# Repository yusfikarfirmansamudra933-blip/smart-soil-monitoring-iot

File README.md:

# Smart Soil Monitoring IoT

Aplikasi web profesional bergaya **Industrial IoT** untuk memantau kondisi tanah, energi tenaga surya, dan status pulsa modem secara *real-time* maupun historis menggunakan **ESP32-S3 N16R8**, **2× Sensor Arus & Tegangan DC INA226**, **Solar Charge Controller MPPT CN3791**, **Active Buzzer (Alarm Sisa Pulsa Modem 4G)**, **DS18B20 Waterproof**, **Capacitive Soil Moisture Sensor**, **Sensor pH Tanah Output Analog ADC + DMS**, dan **Modem 4G LTE**.

- **Production Web App**: https://smart-soil-monitoring-iot.vercel.app
- **Default Device ID**: `SOIL-001`
- **Database**: Supabase PostgreSQL

---

## Fitur Utama
- **Responsif & PWA**: Mendukung Android, tablet, dan desktop dengan App Manifest (`/manifest.json`), Service Worker (`/sw.js`), Splash Screen, dan deteksi Offline State.
- **Monitoring Tanah Real-Time**:
  1. **Soil pH (Analog ADC + DMS)**: Nilai pH terkini, grafik perubahan, status Asam/Netral/Basa, riwayat pengukuran, dan status koneksi sensor.
  2. **Soil Moisture (Capacitive Soil Moisture + DMS)**: Pembacaan kelembapan terkalibrasi (`%`) & nilai mentah (`Raw Value`), status Kering/Normal/Basah, riwayat, dan status koneksi.
  3. **Soil Temperature (DS18B20 Waterproof)**: Suhu tanah dalam °C, grafik perubahan, status suhu, riwayat, dan status sensor.
- **Dual-Channel Energy Monitoring (2× INA226 + CN3791 MPPT)**:
  - **INA226 #1 (`0x40`)**: Memantau **Tegangan (V), Arus (A), dan Daya (W) Panel Surya** secara real-time.
  - **INA226 #2 (`0x41`)**: Memantau **Tegangan (V), Arus (A), dan Daya (W) Baterai** secara real-time.
  - Tidak membuat data energi palsu (menampilkan `Not Available` jika INA226 belum terdeteksi).
- **Fitur Peringatan Pulsa Modem 4G + Active Buzzer**:
  - Memantau sisa pulsa Modem 4G (`modem_credit_rp`) dan otomatis membunyikan **Active Buzzer (`GPIO 21`)** serta memicu alarm kritis di dashboard saat pulsa turun di bawah ambang batas (default `< Rp 10.000`).
- **Grafik & Riwayat Interaktif**: Filter rentang waktu (`1 jam`, `6 jam`, `24 jam`, `7 hari`, `30 hari`), filter tanggal, tabel riwayat, **Export CSV**, dan **Export PDF**.
- **Sistem Alarm Otomatis (10 Parameter)**: Evaluasi otomatis pH, kelembapan, suhu, tegangan baterai, status ESP32-S3, koneksi sensor, modem 4G, dan **sisa pulsa modem (Active Buzzer)**.
- **Demo Mode vs Live Hardware Mode**: Semua data simulasi berlabel `DEMO` (`is_demo: true`) dan dipisahkan dari data perangkat nyata (`is_demo: false`) di PostgreSQL.

---

## Komponen Utama Perangkat Keras
1. **ESP32-S3 N16R8** — Otak utama (Dual-core, 16MB Flash, 8MB OPI PSRAM, I2C, ADC1, UART).
2. **2× Sensor Arus & Tegangan DC INA226** — 16-bit I2C bidirectional monitor (`0x40` untuk **Panel Surya**, `0x41` untuk **Baterai**).
3. **CN3791** — MPPT Solar Charge Controller untuk pengisian baterai efisien dari panel surya.
4. **Active Buzzer** — Alarm suara lokal ketika sisa pulsa Modem 4G menipis.
5. **DS18B20 Waterproof** — Sensor suhu tanah digital tahan air (1-Wire).
6. **Capacitive Soil Moisture Sensor** — Sensor kelembapan tanah kapasitif anti-korosi.
7. **Sensor pH Tanah Output Analog ADC + DMS** — Arsitektur *Driver Sensor Modular*.
8. **Modem 4G LTE (MiFi Bolt ZTE MF90 Unlock All Operator)** — Koneksi internet lapangan & pembacaan SMS kuota/pulsa operator.
9. **Panel Surya & Baterai** — Sumber daya mandiri 24 jam.
10. **DC-DC Converter 5V, Sekering (Fuse), & Distribusi Daya**.

---

## Diagram Blok Wiring Keseluruhan

```text
                SISTEM TENAGA SURYA, CN3791 MPPT & 2× INA226
  ┌─────────────────┐     ┌──────────────────────┐     ┌───────────────────────┐
  │   Panel Surya   │────▶│  INA226 #1 (0x40)    │────▶│  CN3791 MPPT Charger  │
  │    (PV+ / PV-)  │     │  (Ukur V, A, W PV)   │     │  [IN+ / IN-]          │
  └─────────────────┘     └──────────┬───────────┘     │  [BAT+ / BAT-]        │
                                     │ I2C (SDA/SCL)   └───────────┬───────────┘
                                     │                             ▼
                                     │                 ┌───────────────────────┐
                                     │                 │  INA226 #2 (0x41)     │
                                     │                 │  (Ukur V, A, W Batt)  │
                                     │                 └─────┬───────────┬─────┘
                                     │ I2C (GPIO 8/9)        │ I2C       │ Fuse
                                     └───────────────────────┘           ▼
                                                               ┌───────────────────┐
                                                               │ Baterai + DC-DC   │
                                                               │ Regulasi 5V Stabil│
                                                               └────┬─────────┬────┘
                                                            5V/GND  │         │ 5V/GND
                                                     ┌──────────────┘         └──────────────┐
                                                     ▼                                       ▼
                                           ┌──────────────────┐                    ┌─────────────────────────────┐
                                           │    Modem 4G      │◀─ WiFi / UART2 ───▶│       ESP32-S3 N16R8        │
                                           │  (Cek Pulsa+Net) │  (GPIO 17 / 18)    │  5V | 3.3V | GND | I2C 8/9  │
                                           └──────────────────┘                    └─┬──────┬──────┬──────┬──────┘
                                                                                     │      │      │      │
                ┌────────────────────────────────────────────────────────────────────┘      │      │      └──────────────────┐
                ▼                                 ▼                                         ▼                                ▼
    ┌───────────────────────┐         ┌────────────────────────┐               ┌──────────────────────────┐      ┌──────────────────────┐
    │   DS18B20 Waterproof  │         │ Capacitive Soil Moist. │               │  pH Analog ADC + DMS     │      │    Active Buzzer     │
    │  DATA ──▶ GPIO 4      │         │   AOUT ──▶ GPIO 5      │               │ pH ──▶ GPIO 6 (ADC1)     │      │  SIG ──▶ GPIO 21     │
    │  + Pull-up 4.7kΩ 3.3V │         │   VCC ──▶ 3.3V         │               │ DMS ──▶ GPIO 7 (ADC1)    │      │ (Alarm Pulsa Menipis)│
    └───────────────────────┘         └────────────────────────┘               └──────────────────────────┘      └──────────────────────┘
```

---

## 1. Wiring Tenaga Surya, CN3791 MPPT & 2× INA226

### A. Jalur Daya Utama (High-Side Current Sensing)
| Dari Komponen | Ke Komponen | Keterangan |
|---|---|---|
| Panel Surya (`PV+`) | **INA226 #1 (`0x40`)** `VIN+` | Jalur positif panel masuk ke shunt INA226 #1 |
| **INA226 #1 (`0x40`)** `VIN-` | **CN3791** Terminal `IN+` (`PV+`) | Arus panel terukur sebelum masuk ke CN3791 |
| Panel Surya (`PV-`) | **CN3791** `IN-` (`GND`) | Satukan ke Common Ground (`GND`) |
| **CN3791** Terminal `BAT+` | **INA226 #2 (`0x41`)** `VIN+` | Jalur pengisian/pemakaian baterai masuk ke shunt INA226 #2 |
| **INA226 #2 (`0x41`)** `VIN-` | **Sekering (Fuse)** → Baterai (`+`) & Input DC-DC 5V | Mengukur tegangan, arus charge (+), dan arus discharge (-) baterai |
| Baterai (`-`) | **CN3791** `BAT-` (`GND`) & Common Ground | Semua `GND` (CN3791, 2× INA226, ESP32-S3, Modem 4G) wajib tersambung |
| Output DC-DC 5V (`5V` / `GND`) | Pin `5V` ESP32-S3 N16R8 & Daya `5V` Modem 4G | Pastikan output stabil **5.0V (≥ 2A)** sebelum disambung |

### B. Wiring Dual Bus I2C 2× INA226 ke ESP32-S3 N16R8 (Tanpa Jumper `A0`)
Kedua modul INA226 tetap memakai alamat standar `0x40` dengan memanfaatkan 2 jalur Hardware I2C terpisah pada ESP32-S3 (`Wire` & `Wire1`):

| Pin INA226 | INA226 #1 — Panel Surya (`Wire` / `0x40`) | INA226 #2 — Baterai 3S (`Wire1` / `0x40`) |
|---|---|---|
| `VCC` | `3.3V` ESP32-S3 | `3.3V` ESP32-S3 |
| `GND` | `GND` ESP32-S3 | `GND` ESP32-S3 |
| `SDA` | **`GPIO 8`** ESP32-S3 | **`GPIO 10`** ESP32-S3 |
| `SCL` | **`GPIO 9`** ESP32-S3 | **`GPIO 11`** ESP32-S3 |
| `VBS` (`VBUS`) | Sambung ke `IN-` / `IN+` (PV+) | Sambung ke `IN-` / `IN+` (BAT+) |

---

## 2. Wiring Sensor Tanah, Active Buzzer & Modem 4G ke ESP32-S3 N16R8

> **PERINGATAN PIN ESP32-S3 N16R8:**
> Pada varian **N16R8 (Octal OPI PSRAM)**, **`GPIO 35`, `GPIO 36`, dan `GPIO 37` digunakan internal oleh PSRAM** dan **TIDAK BOLEH** dipakai untuk sensor. Semua pin di bawah ini 100% aman dan berada di `ADC1` (tidak bentrok dengan WiFi).

| Komponen | Pin Modul | Pin ESP32-S3 N16R8 | Keterangan |
|---|---|---|---|
| **DS18B20 Waterproof** | `VCC` (Merah) / `GND` (Hitam) / `DATA` (Kuning) | `3.3V` / `GND` / **`GPIO 4`** | Wajib pasang resistor **pull-up 4.7 kΩ** antara `GPIO 4` dan `3.3V` |
| **Capacitive Soil Moisture** | `VCC` / `GND` / `AOUT` | `3.3V` / `GND` / **`GPIO 5`** | `ADC1_CH4` — gunakan suplai 3.3V agar output ≤3.3V |
| **Modul DMS (Depoinovasi)** | Kabel 1: `Hitam / Coklat` | **`GND`** | Ground Modul DMS |
| **Modul DMS (Depoinovasi)** | Kabel 2: `Putih / Merah` | **`3.3V`** | Tegangan suplai `Vin / 3V3` Modul DMS |
| **Modul DMS + Probe pH** | Kabel 3: `Abu-abu / Oren` | **Kabel `Hitam` Probe pH** | Kabel `Putih` Probe pH disambung langsung ke **`GND` ESP32-S3** |
| **Modul DMS (ADC pH)** | Kabel 4: `Ungu / Kuning` | **`GPIO 6`** (`ADC1_CH5`) | Pengganti `D34` pada ESP32 biasa (aman dari PSRAM ESP32-S3) |
| **Modul DMS (Digital/D13)** | Kabel 5: `Biru / Hijau` | **`GPIO 7`** | Pengganti `D13` pada ESP32 biasa |
| **Active Buzzer (Alarm Pulsa)** | `VCC / (+)` / `GND / (-)` | **`GPIO 21`** / `GND` | Gunakan transistor NPN `S8050` + resistor `1 kΩ` untuk buzzer 5V 2-pin |
| **Modem 4G (MiFi Bolt ZTE MF90)** | Port Micro-USB `5V` / WiFi AP | `5V DC-DC` / WiFi | Suplai `5V` stabil dari DC-DC Buck Converter; ESP32-S3 konek ke WiFi MiFi ZTE MF90 & baca SMS operator via `192.168.1.1` / `192.168.0.1` |

---

## 3. Cara Upload Firmware ke ESP32-S3 N16R8

File firmware berada di folder `firmware/esp32_smart_soil/`:
- [esp32_smart_soil.ino](firmware/esp32_smart_soil/esp32_smart_soil.ino)
- [sensor_drivers.h](firmware/esp32_smart_soil/sensor_drivers.h)
- [modem_quota_reader.h](firmware/esp32_smart_soil/modem_quota_reader.h) — Pembaca SMS notifikasi kuota & pulsa operator dari Modem 4G kartu SIM
- [offline_logger.h](firmware/esp32_smart_soil/offline_logger.h) — **Offline Data Logger & Auto-Sync di 16MB Flash (`LittleFS`)** saat sinyal 4G terputus/kuota habis

### Cara Kerja Pembacaan Sisa Kuota dari SMS MiFi Bolt ZTE MF90
1. ESP32-S3 terhubung ke WiFi **MiFi Bolt 4G ZTE MF90** lalu otomatis membaca kotak masuk SMS kartu SIM pada WebUI ZTE MF90 (`/goform/goform_get_cmd_process?cmd=sms_data_total`, IP otomatis `192.168.1.1` / `192.168.0.1`) setiap 2 menit melalui `ModemQuotaReader` (lengkap dengan dekoder **UCS2 Hex → Teks** bawaan ZTE).
2. Saat operator mengirim SMS peringatan (misal *"Sisa kuota internet Anda 350 MB"* atau *"Sisa pulsa Anda Rp 8.500"*), parser otomatis mengekstrak angka **MB/GB** dan **Rp** lalu menyimpannya ke memori NVS Flash ESP32-S3 agar tidak hilang saat restart.
3. Batas minimum kuota (`MB`), batas pulsa (`Rp`), dan sakelar Active Buzzer dapat diatur langsung dari web pada menu **Device Management** — ESP32-S3 otomatis menyinkronkannya via `GET /api/v1/device/config`.
4. Jika kuota atau pulsa berada di bawah batas minimum, **Active Buzzer (`GPIO 21`)** otomatis berbunyi 3× beep peringatan. *(Anda juga bisa mengetes parsernya langsung lewat Serial Monitor dengan mengetik contoh kalimat SMS operator lalu menekan Enter).*

### Langkah 1 — Siapkan Arduino IDE & Library
1. Instal **Arduino IDE 2.x** dari https://www.arduino.cc/en/software.
2. Buka **File → Preferences** → tambahkan URL berikut pada **Additional Boards Manager URLs**:
   ```text
   https://espressif.github.io/arduino-esp32/package_esp32_index.json
   ```
3. Buka **Tools → Board → Boards Manager...**, cari **`esp32`** (*by Espressif Systems*), lalu klik **Install**.
4. Buka **Tools → Manage Libraries...**, lalu instal 3 library wajib berikut:
   - **`INA226_WE`** (*by Wolfgang Ewald*) — untuk 2× sensor arus/tegangan INA226
   - **`OneWire`** (*by Paul Stoffregen*)
   - **`DallasTemperature`** (*by Miles Burton*)

### Langkah 2 — Konfigurasi Firmware
Buka `firmware/esp32_smart_soil/esp32_smart_soil.ino` dan sesuaikan bagian konfigurasi:
```cpp
const char* DEVICE_ID         = "SOIL-001";
const char* API_KEY           = "sk_soil_001_esp32_4g_key_2026";
const char* BASE_API_URL      = "https://smart-soil-monitoring-iot.vercel.app";

const char* MODEM_AP_SSID     = "NAMA_WIFI_MODEM_4G_ANDA";
const char* MODEM_AP_PASS     = "PASSWORD_MODEM_4G_ANDA";

// Default siap pakai untuk MiFi Bolt 4G ZTE MF90:
const ModemSmsSourceMode MODEM_SMS_MODE = MODEM_SMS_HTTP_ZTE;
const char* MODEM_ROUTER_IP             = "auto";  // Otomatis deteksi 192.168.1.1 / 192.168.0.1
const char* MODEM_WEB_PASSWORD          = "admin"; // Password WebUI ZTE MF90 (default: "admin")
```

### Langkah 3 — Pengaturan Board Khusus ESP32-S3 N16R8 & Upload
1. Sambungkan **ESP32-S3 N16R8** ke laptop menggunakan **kabel USB-C data** (colok ke port `USB` atau `UART/COM` di board).
2. Di menu **Tools**, atur persis sesuai spesifikasi **N16R8**:
   - **Board**: `ESP32S3 Dev Module`
   - **Flash Size**: `16MB (128Mb)`
   - **Partition Scheme**: `16M Flash (3MB APP/9.9MB FATFS)` *(atau partisi 16MB yang mendukung LittleFS)*
   - **PSRAM**: `OPI PSRAM`
   - **USB CDC On Boot**: `Enabled` *(agar Serial Monitor muncul jika memakai port USB native)*
   - **Upload Speed**: `921600` (atau `115200` jika kurang stabil)
   - **Port**: Pilih port `COMx` ESP32-S3 Anda.
3. Klik tombol **Upload (`→`)**.
   > **Tips Mode Bootloader ESP32-S3**: Jika gagal terhubung, tekan & tahan tombol **`BOOT`**, tekan sebentar tombol **`RST`**, lalu lepaskan **`BOOT`** agar ESP32-S3 masuk mode download, kemudian klik **Upload**.

### Langkah 4 — Verifikasi di Serial Monitor & Dashboard Web
1. Buka **Tools → Serial Monitor** (`115200 baud`).
2. Pastikan muncul log:
   - `[INA226 #1] Panel Surya (0x40) OK`
   - `[INA226 #2] Baterai (0x41) OK`
   - `[TELEMETRY PAYLOAD] {...}` dan `[HTTP POST] Status code: 201`.
3. Buka web **Smart Soil Monitoring IoT** → beralih ke mode **LIVE HARDWARE** → cek menu **Energy Monitoring** (2× INA226), **Soil Monitoring**, dan **Alerts** (termasuk status **Active Buzzer & Pulsa Modem 4G**).

---

## Menjalankan Aplikasi Web Secara Lokal
```bash
npm install
npm run dev
```
Lalu buka `http://localhost:3000` di browser.

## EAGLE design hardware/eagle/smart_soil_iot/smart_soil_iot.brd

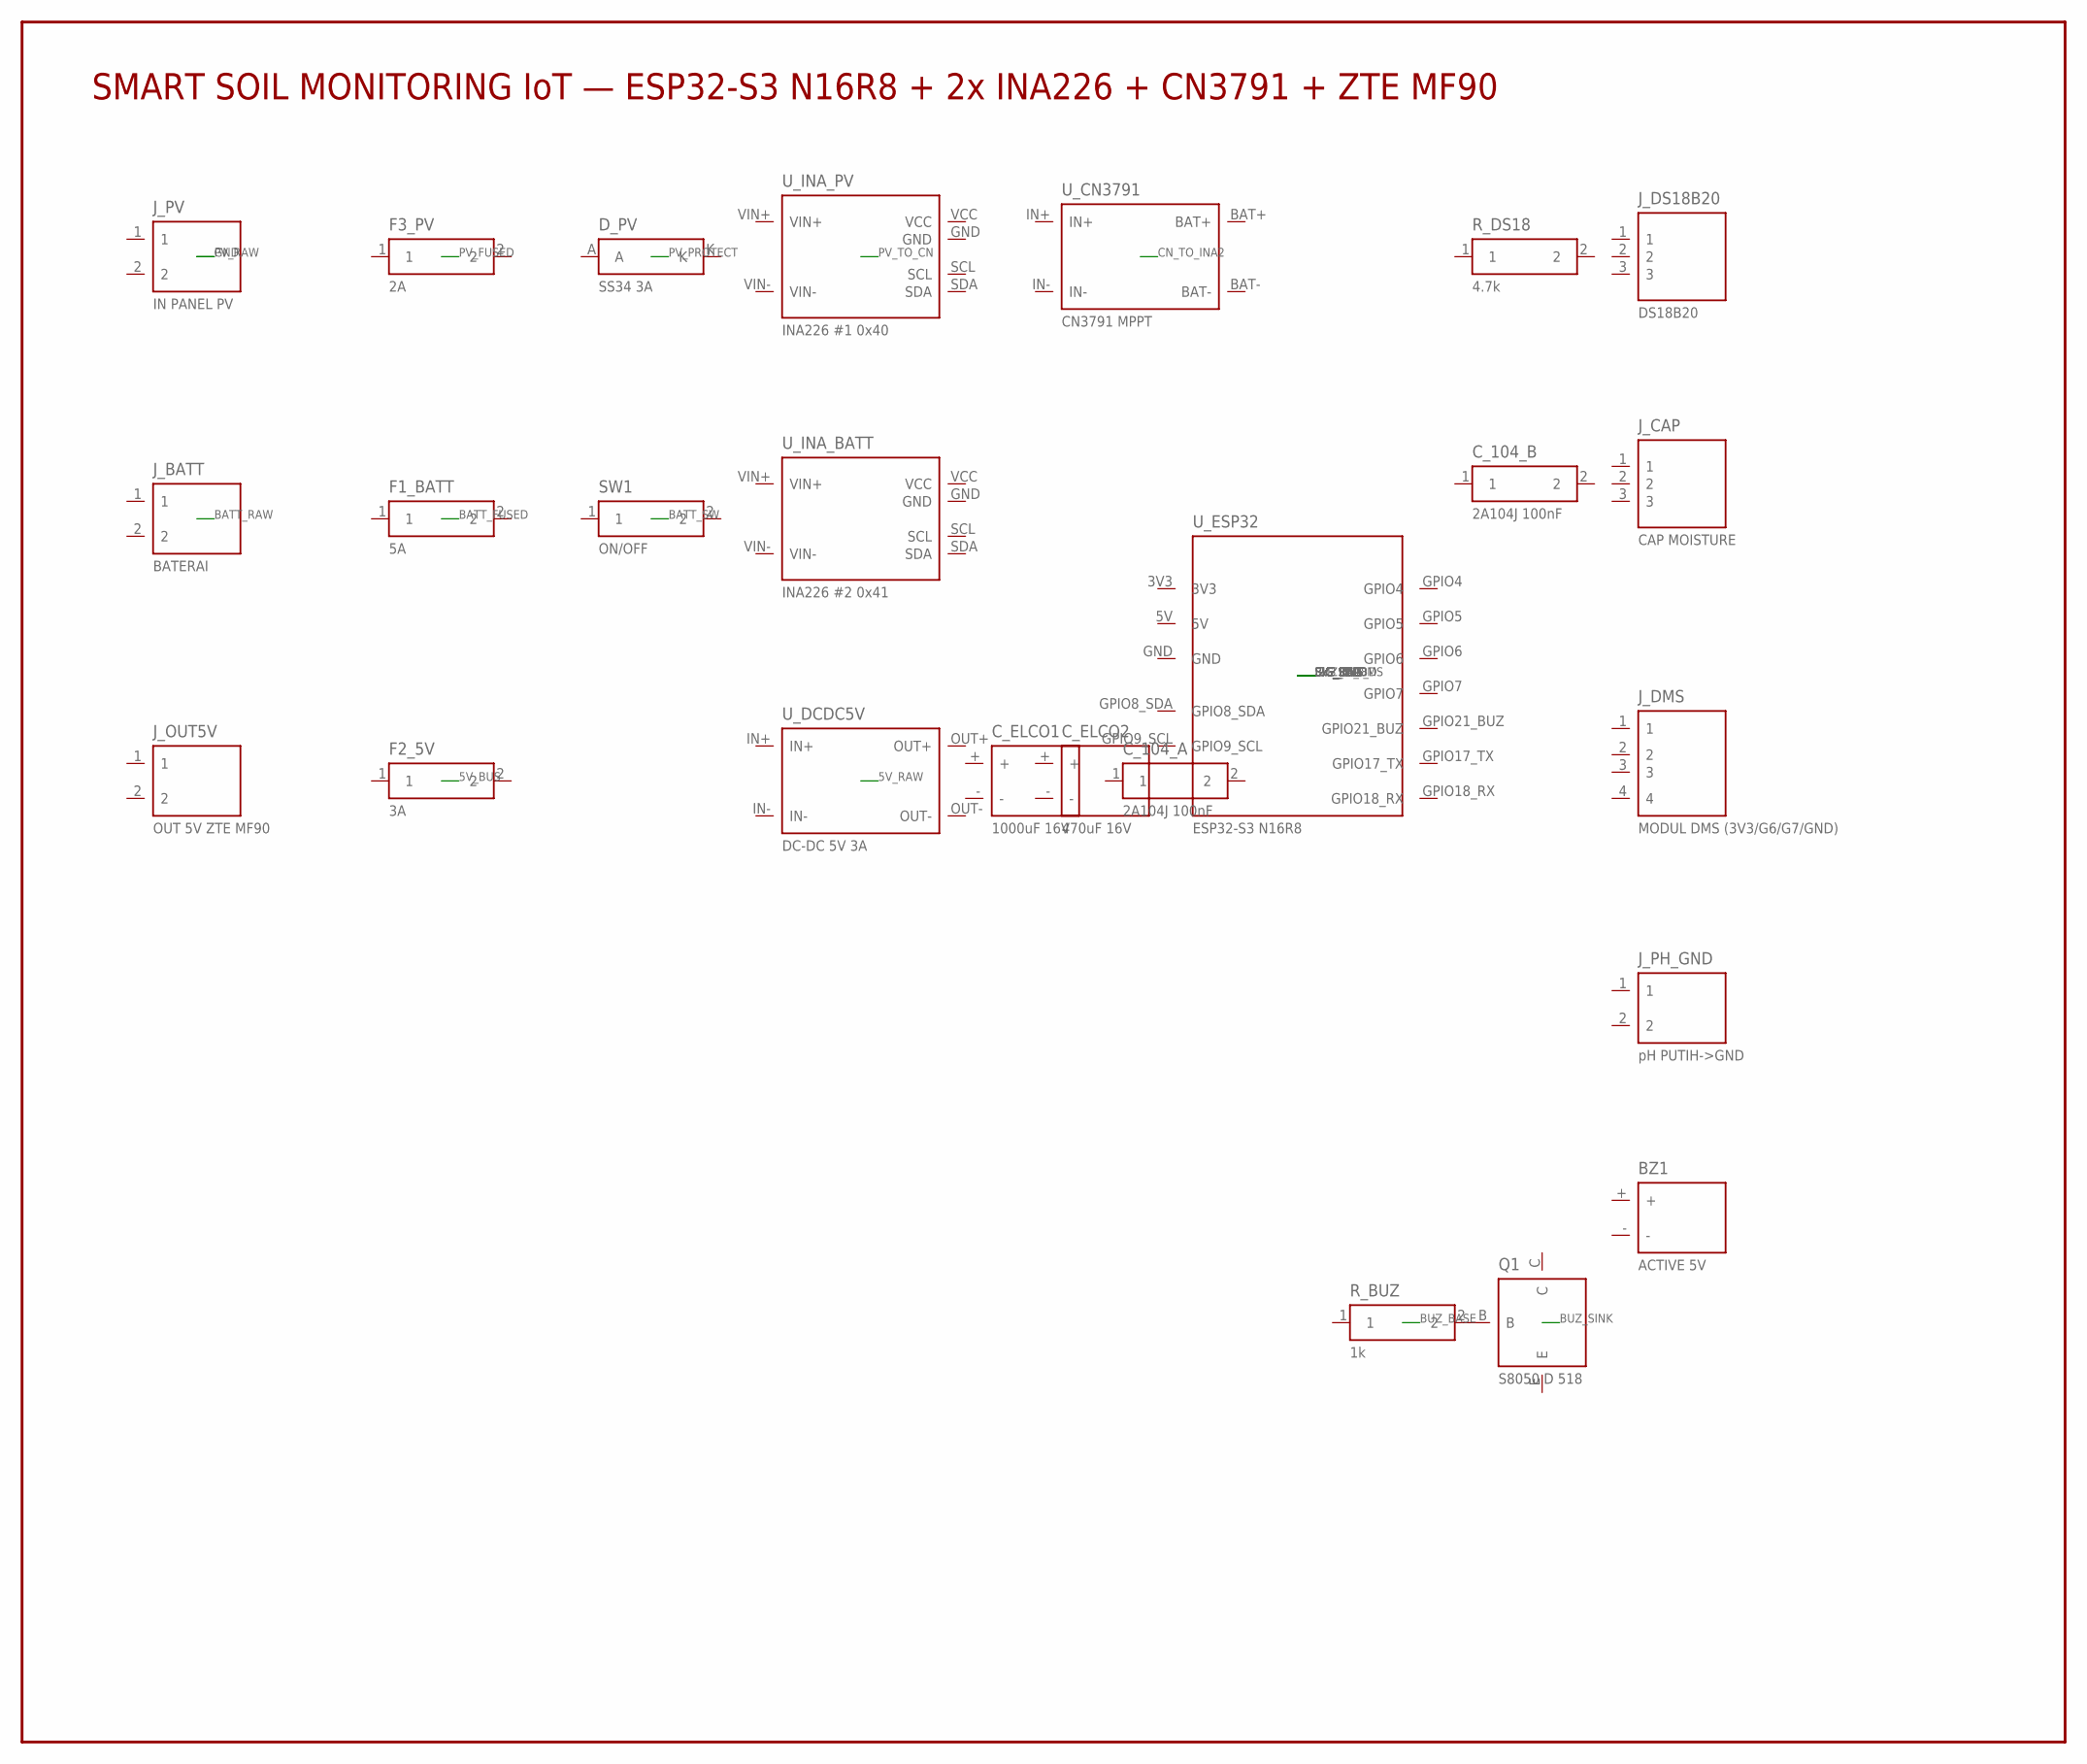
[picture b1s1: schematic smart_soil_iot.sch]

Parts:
BZ1: ACTIVE 5V; BUZZER_5V
C_104_A, C_104_B: 2A104J 100nF; MYLAR_104
C_ELCO1: 1000uF 16V; ELCO_CAP
C_ELCO2: 470uF 16V; ELCO_CAP
D_PV: SS34 3A; DIODE_SS34
F1_BATT: 5A; FUSE_HOLDER
F2_5V: 3A; FUSE_HOLDER
F3_PV: 2A; FUSE_HOLDER
J_BATT: BATERAI; TERM_2P
J_CAP: CAP MOISTURE; TERM_3P
J_DMS: MODUL DMS (3V3/G6/G7/GND); TERM_4P
J_DS18B20: DS18B20; TERM_3P
J_OUT5V: OUT 5V ZTE MF90; TERM_2P
J_PH_GND: pH PUTIH->GND; TERM_2P
J_PV: IN PANEL PV; TERM_2P
Q1: S8050 D 518; TO92_S8050
R_BUZ: 1k; AXIAL_RES
R_DS18: 4.7k; AXIAL_RES
SW1: ON/OFF; SWITCH_2P
U_CN3791: CN3791 MPPT; CN3791_MOD
U_DCDC5V: DC-DC 5V 3A; DCDC_5V_MOD
U_ESP32: ESP32-S3 N16R8; ESP32_S3_N16R8
U_INA_BATT: INA226 #2 0x41; INA226_MOD
U_INA_PV: INA226 #1 0x40; INA226_MOD

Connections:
3V3_BUS: C_104_B.1, J_CAP.1, J_DMS.1, J_DS18B20.1, R_DS18.1, U_ESP32.3V3, U_INA_BATT.VCC, U_INA_PV.VCC
5V_BUS: BZ1.+, C_104_A.1, C_ELCO1.+, C_ELCO2.+, F2_5V.2, J_OUT5V.1, U_ESP32.5V
5V_RAW: F2_5V.1, U_DCDC5V.OUT+
BATT_FUSED: F1_BATT.2, SW1.1
BATT_RAW: F1_BATT.1, J_BATT.1
BATT_SW: SW1.2, U_DCDC5V.IN+, U_INA_BATT.VIN-
BUZ_BASE: Q1.B, R_BUZ.2
BUZ_SIG: R_BUZ.1, U_ESP32.GPIO21_BUZ
BUZ_SINK: BZ1.-, Q1.C
CN_TO_INA2: U_CN3791.BAT+, U_INA_BATT.VIN+
GND: C_104_A.2, C_104_B.2, C_ELCO1.-, C_ELCO2.-, J_BATT.2, J_CAP.3, J_DMS.4, J_DS18B20.3, J_OUT5V.2, J_PH_GND.1, J_PH_GND.2, J_PV.2, Q1.E, U_CN3791.BAT-, U_CN3791.IN-, U_DCDC5V.IN-, U_DCDC5V.OUT-, U_ESP32.GND, U_INA_BATT.GND, U_INA_PV.GND
I2C_SCL: U_ESP32.GPIO9_SCL, U_INA_BATT.SCL, U_INA_PV.SCL
I2C_SDA: U_ESP32.GPIO8_SDA, U_INA_BATT.SDA, U_INA_PV.SDA
PV_FUSED: D_PV.A, F3_PV.2
PV_PROTECT: D_PV.K, U_INA_PV.VIN+
PV_RAW: F3_PV.1, J_PV.1
PV_TO_CN: U_CN3791.IN+, U_INA_PV.VIN-
SIG_CAP: J_CAP.2, U_ESP32.GPIO5
SIG_DMS_D: J_DMS.3, U_ESP32.GPIO7
SIG_DS18: J_DS18B20.2, R_DS18.2, U_ESP32.GPIO4
SIG_PH_DMS: J_DMS.2, U_ESP32.GPIO6

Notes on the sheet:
SMART SOIL MONITORING IoT — ESP32-S3 N16R8 + 2x INA226 + CN3791 + ZTE MF90

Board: 2 copper layers, 25 parts (0 on the bottom side), 21 nets, no tracks yet.

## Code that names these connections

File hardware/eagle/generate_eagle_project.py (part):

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<package name="ESP32_S3_N16R8">
{pkg_rect(56.0, 28.0)}
<pad name="3V3" x="-22.86" y="12.7" drill="1.0" diameter="1.7" shape="square"/>
<pad name="GPIO4" x="-17.78" y="12.7" drill="1.0" diameter="1.7"/>
<pad name="GPIO5" x="-12.70" y="12.7" drill="1.0" diameter="1.7"/>
<pad name="GPIO6" x="-7.62" y="12.7" drill="1.0" diameter="1.7"/>
<pad name="GPIO7" x="-2.54" y="12.7" drill="1.0" diameter="1.7"/>
<pad name="GPIO8_SDA" x="5.08" y="12.7" drill="1.0" diameter="1.7"/>
<pad name="GPIO9_SCL" x="10.16" y="12.7" drill="1.0" diameter="1.7"/>
<pad name="5V" x="-22.86" y="-12.7" drill="1.0" diameter="1.7"/>
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<symbol name="ESP32_S3_N16R8">{sym_box([
    ("3V3", -20.32, 12.7, "R0"), ("5V", -20.32, 7.62, "R0"), ("GND", -20.32, 2.54, "R0"),
    ("GPIO8_SDA", -20.32, -5.08, "R0"), ("GPIO9_SCL", -20.32, -10.16, "R0"),
    ("GPIO4", 20.32, 12.7, "R180"), ("GPIO5", 20.32, 7.62, "R180"), ("GPIO6", 20.32, 2.54, "R180"),
    ("GPIO7", 20.32, -2.54, "R180"), ("GPIO21_BUZ", 20.32, -7.62, "R180"),
    ("GPIO17_TX", 20.32, -12.7, "R180"), ("GPIO18_RX", 20.32, -17.78, "R180")
], 30.48, 40.64)}</symbol>
"""
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    devset("CN3791_MOD", "CN3791_MOD", "CN3791_MOD", [("IN+", "IN+"), ("IN-", "IN-"), ("BAT+", "BAT+"), ("BAT-", "BAT-")], "U"),
    devset("DCDC_5V_MOD", "DCDC_5V_MOD", "DCDC_5V_MOD", [("IN+", "IN+"), ("IN-", "IN-"), ("OUT+", "OUT+"), ("OUT-", "OUT-")], "U"),
    devset("ESP32_S3_N16R8", "ESP32_S3_N16R8", "ESP32_S3_N16R8", [
        ("3V3", "3V3"), ("5V", "5V"), ("GND", "GND"), ("GPIO4", "GPIO4"), ("GPIO5", "GPIO5"),
        ("GPIO6", "GPIO6"), ("GPIO7", "GPIO7"), ("GPIO8_SDA", "GPIO8_SDA"), ("GPIO9_SCL", "GPIO9_SCL"),
        ("GPIO17_TX", "GPIO17_TX"), ("GPIO18_RX", "GPIO18_RX"), ("GPIO21_BUZ", "GPIO21_BUZ")
    ], "U"),
])
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        ("Q1", "E")
    ],

    "I2C_SDA":    [("U_ESP32", "GPIO8_SDA"), ("U_INA_PV", "SDA"), ("U_INA_BATT", "SDA")],
    "I2C_SCL":    [("U_ESP32", "GPIO9_SCL"), ("U_INA_PV", "SCL"), ("U_INA_BATT", "SCL")],

    "SIG_DS18":   [("U_ESP32", "GPIO4"), ("J_DS18B20", "2"), ("R_DS18", "2")],
    "SIG_CAP":    [("U_ESP32", "GPIO5"), ("J_CAP", "2")],
    "SIG_PH_DMS": [("U_ESP32", "GPIO6"), ("J_DMS", "2")],
    "SIG_DMS_D":  [("U_ESP32", "GPIO7"), ("J_DMS", "3")],

    "BUZ_SIG":    [("U_ESP32", "GPIO21_BUZ"), ("R_BUZ", "1")],
    "BUZ_BASE":   [("R_BUZ", "2"), ("Q1", "B")],
    "BUZ_SINK":   [("Q1", "C"), ("BZ1", "-")],
}
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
